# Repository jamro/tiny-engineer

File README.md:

# Tiny Engineer

> Give your AI coding agent a body.

**[Watch the demo](https://youtu.be/RX_QRxdXMjg)** · [Build your own](#build-your-own) · [Community builds](#community-builds) · [How it works](#how-it-works)

A small robot on your desk. It moves, changes its face, and rings a bell as your coding AI agent works.

| Your agent… | The robot… |
| --- | --- |
| Reads files | Looks around |
| Writes code | Types |
| Thinks or waits | Looks up |
| Finishes the task | Rings the bell |

Open source. Print the body, plug the ESP32, servos, OLED, and speaker into the [main control board](docs/hardware/main-control-board.md), flash it, and it joins your Wi-Fi.

**Works with** Claude Code · Cursor · Antigravity — via [`npx -y tiny-engineer setup`](docs/integration.md) — or Codex, Windsurf, and any script that can POST ([integration guide](docs/integration.md) · [HTTP API](docs/api.md)), including speech through [`POST /play`](docs/api.md#post-play).

## Build your own

| | |
| --- | --- |
| **Parts (electronics + 5× SG90 Servos)** | [shopping list](docs/shopping.md): [main control board](docs/hardware/order-main-control-board.md) plus ESP32, servos, OLED, and speaker |
| **Also needed** | 3D printer + filament, or [order prints](docs/3d/order-parts.md); M2 screws; **5 V / ≥2 A** USB supply |
| **Tools** | Plug in the ESP32, servos, OLED, and speaker on the [main control board](docs/hardware/main-control-board.md). Want to add extra modules? [advanced wiring](docs/hardware/wiring.md) |
| **Difficulty** | **Medium** - fair first hardware project for a software engineer, not a one-LED kit. Optional primer: [From Code to Circuits](docs/hardware-for-software-engineers/README.md) |

The default build uses the open-source main control board. Order it from any fab ([how to order](docs/hardware/order-main-control-board.md) · [KiCad](hardware/boards/main-control-board/)). 

If a ~$15–20 assembled board like this would be useful to you, [Vote here 👍 →](https://github.com/jamro/tiny-engineer/discussions/50) → I’m using the interest to decide whether it’s worth developing further.

**Print → Connect → Flash → Assemble** - step-by-step: **[Getting started](docs/getting-started.md)**.

## Community builds

Finished builds, mods, and desk setups live in **[Show and tell](https://github.com/jamro/tiny-engineer/discussions/categories/show-and-tell)** on GitHub Discussions - browse what others made and post photos of yours.

**Built one? [Share in Show and tell →](https://github.com/jamro/tiny-engineer/discussions/categories/show-and-tell)**

## Roadmap

What we are building toward:

- **More agent integrations** - one-command hooks for more IDEs and CLIs
- **Simplified build process** - easier assembly and setup for quicker builds
- **New characters / bodies** - alternate shells and mods
- **Multi-agent desk** - more than one tiny teammate

**[Star Tiny Engineer](https://github.com/jamro/tiny-engineer)** to follow the build.

## How it works

Your agent (or a hook script) sends poses over **Wi‑Fi HTTP** or **USB serial**. The **ESP32-C3** runs the firmware, optional Wi‑Fi/REST, USB CDC control, and drives the servos, face, and speaker.

**Clients**

- **Default** — [`npx -y tiny-engineer`](https://www.npmjs.com/package/tiny-engineer) (`setup` / `hook`) for Cursor, Claude Code, Antigravity (HTTP or `--transport serial`)
- **Advanced** — `POST /anim` ([HTTP API](docs/api.md)) or framed USB serial ([serial.md](docs/serial.md))

Details: [Integrations](docs/integration.md) · [HTTP API](docs/api.md) · [USB serial](docs/serial.md) · [Cursor hooks](docs/hooks.md)

## Documentation

| You want to… | Start here |
| --- | --- |
| Build the robot | [Getting started](docs/getting-started.md) |
| Buy parts | [Shopping list](docs/shopping.md) |
| Flash the board | **[Web flash](https://jamro.github.io/tiny-engineer/flash/)** · [Flash](docs/flash.md) |
| Assemble the prints | [Assembly](docs/3d/assembly.md) |
| Print the parts | [3D models](3d_models/README.md) |
| Hook up an agent | [Integrations](docs/integration.md) |
| Call the HTTP API | [API](docs/api.md) |
| Anything else | [Docs index](docs/README.md) |

Print it, connect it, change the CAD, or hook up another agent. Issues and PRs welcome - especially new integrations. [CONTRIBUTING.md](CONTRIBUTING.md) · [SECURITY.md](SECURITY.md) · [CODE_OF_CONDUCT.md](CODE_OF_CONDUCT.md)

## License

- **Software** (firmware, integrations, scripts, documentation) — [MIT](LICENSE)
- **Hardware designs** (CAD source and printables in [`3d_models/`](3d_models/) and under [`mods/*/3d_models/`](mods/); KiCad PCBs in [`hardware/`](hardware/)) — [CERN-OHL-S-2.0](3d_models/LICENSE)

See [LICENSING.md](LICENSING.md) for scope and effective date. The **Tiny Engineer** name and logo are not licensed - see [TRADEMARK.md](TRADEMARK.md).

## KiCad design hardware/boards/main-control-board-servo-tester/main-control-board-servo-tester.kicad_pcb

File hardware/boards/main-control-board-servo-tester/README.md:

# main-control-board-servo-tester

Plug that seats on one servo column of the main control board. A red LED shows 5 V. A yellow LED shows the signal.

- **Status:** draft
- **KiCad:** 10
- **Interfaces:** J1, 1x03 socket. Pin 1 signal (schematic net `+3.3V`) through R1 470 Ω to yellow D1. Pin 2 `+5V` through R2 1 kΩ to red D2. Pin 3 GND. Both LED cathodes go to GND.
- **Assumptions:** Seat J1 so the silk labels match the main-board column: PWM to PWM, +5V to 5 V, GND to GND. Read those labels on both boards before plugging in. The capacitor beside the servo header blocks the other orientation. Pin 1 on this tester is the signal pin; it meets the PWM pin of the column, not pin 1. Only the Default net class. Power comes from the column under test.
- **Built:** not manufactured
- **Tested:** not tested

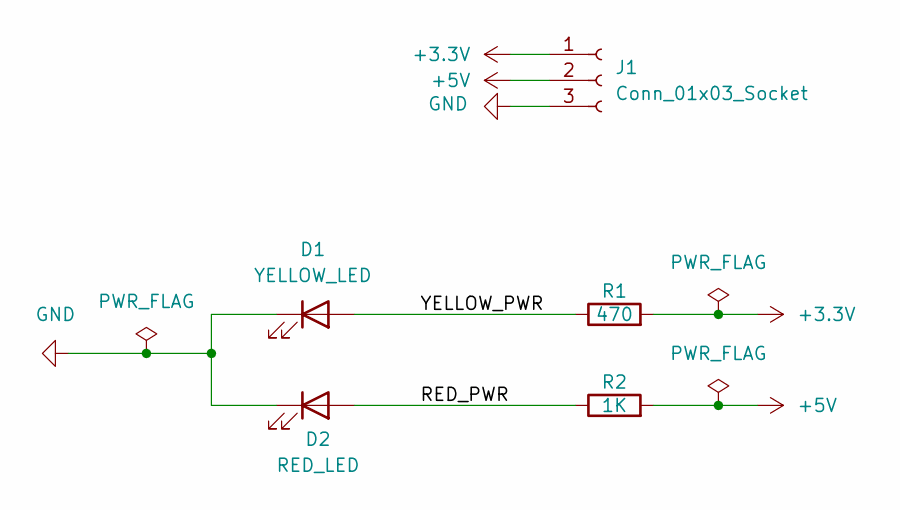
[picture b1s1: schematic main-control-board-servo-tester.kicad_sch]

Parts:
D1: YELLOW_LED; LED_0603_1608Metric; MPN KT-0603Y; LCSC Part # C2287
D2: RED_LED; LED_0603_1608Metric; MPN KT-0603R; LCSC Part # C2286
J1: Conn_01x03_Socket; PinSocket_1x03_P2.54mm_Horizontal; MPN PM254-1-03-W-8.5; LCSC Part # C2897385
R1: 470; R_0603_1608Metric; MPN 0603WAF4700T5E; LCSC Part # C23179
R2: 1K; R_0603_1608Metric; MPN 0603WAF1001T5E; LCSC Part # C21190

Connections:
+3.3V: J1.1, R1.2
+5V: J1.2, R2.2
/RED_PWR: D2.2 (A), R2.1
/YELLOW_PWR: D1.2 (A), R1.1
GND: D1.1 (K), D2.1 (K), J1.3

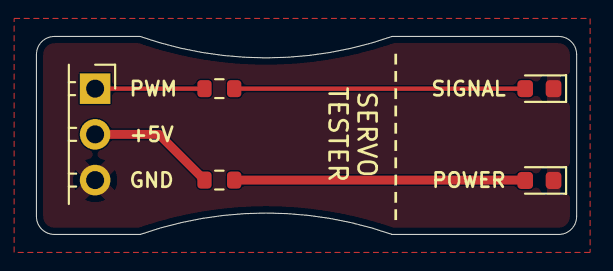
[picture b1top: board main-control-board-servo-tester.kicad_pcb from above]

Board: 2 copper layers, 30.0 x 11.0 mm, 5 parts (0 on the bottom side), 5 nets.

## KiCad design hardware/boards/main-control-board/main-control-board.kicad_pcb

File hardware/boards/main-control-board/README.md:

# main-control-board

This board drives the robot's servos and speaker. Power and USB data come in on a USB-C connector. The Waveshare ESP32-C3-Zero is not soldered down; it plugs into two 9-pin sockets.

- **Status:** tested
- **KiCad:** 10
- **Built:** manufactured and tested
- **Tested:** reference boards ordered and checked; each independent fab run can still differ

## Soldered on the board

The servo driver, the speaker amplifier, and the USB-C connector are parts on this PCB. They replace the plug-in PCA9685 board, the MAX98357A breakout, and the Adafruit 5993 USB-C breakout.

- **PCA9685** drives up to 16 PWM channels. This robot uses five of them for the servos. The I2C address is `0x40`: the address pins and the external-clock pin are tied to ground, so the chip uses its own clock.
- **Servo header** takes five servo plugs. Each plug has ground, 5 V, and a PWM signal.
- **MAX98357A** is the mono class-D amplifier. The speaker connects to a 2-pin header. The speaker's minus terminal is not ground. Connect the speaker only between the two amplifier outputs.
- **USB-C connector** supplies 5 V and the USB data pair. Two 5.1 kΩ resistors on the CC pins mark this board as a USB device. The charger decides how much current is available.
- A **3 A resettable fuse** sits between USB power and the 5 V rail.
- A **TPS259571** eFuse (`U4`) sits between that 5 V rail and servo 5 V. Current limit is set by `R14` (1 kΩ ≈ 2 A). On fault the device auto-retries.
- **OLED header** is for the SSD1306 display. Pin order, from pin 1: 3.3 V, ground, SDA, SCL.
- A second header shares that I2C bus. Its pin order is different: ground, 3.3 V, SDA, SCL.
- A **12-pin extension port** (`J4`) breaks out `SERVO_5V`, two grounds, `+3.3V`, I2S BCLK/LRC, and GPIOs GP6–GP9 / GP20 / GP21.
  - GP8 and GP9 are ESP32-C3 strapping pins. Do not pull them low at reset; GP9 low enters download mode.
  - GP20 and GP21 are the default UART0 RX/TX. Boot log output appears on GP21 at power-up.

A solder jumper next to the amplifier is marked as a 6 dB gain limit.

## What still plugs in

The **Waveshare ESP32-C3-Zero** plugs into two 9-pin sockets, one for each row of pins on the module. This board has no ESP32 chip of its own.

The OLED module plugs into the OLED header.

## Power

USB-C 5 V goes through the fuse onto the `+5V` rail. That rail feeds the ESP32 5 V pin, a 5 V indicator LED, and the eFuse input.

The eFuse output is `SERVO_5V`. That rail feeds the servo plugs (PCA9685 V+), a bulk capacitor, and — through a net tie — the amplifier 5 V net, so the amp supply can still be routed on its own but comes from the protected servo rail, not raw `+5V`.

3.3 V comes from the regulator on the ESP32 module. This board does not have a 3.3 V regulator. 3.3 V feeds the PCA9685 logic supply, the OLED, the I2C pull-ups (4.7 kΩ), the pull-up on the PCA9685 output-enable pin (10 kΩ), and a 3.3 V indicator LED.

Servo 5 V and logic 3.3 V stay separate. They share ground.

Use a **5 V supply of at least 2 A**. Five stalled servos can draw more than a typical USB port provides. Multi-servo stall can also hit the eFuse’s ~2 A limit before the 3 A resettable fuse trips.

## Connections from the ESP32

| Function | ESP32 pin | Goes to |
| --- | --- | --- |
| I2C SDA | GP0 | PCA9685 and OLED |
| I2C SCL | GP1 | PCA9685 and OLED |
| I2S bit clock | GP2 | MAX98357A BCLK |
| I2S word clock | GP3 | MAX98357A LRC |
| I2S data | GP4 | MAX98357A DIN |
| Servo output enable | GP5 | PCA9685 output enable (active low) |
| USB D− | GPIO18 | USB-C |
| USB D+ | GPIO19 | USB-C |

GP5 drives PCA9685 OE (`PCA9685_OE_WIRED` in [`include/pins.h`](../../../include/pins.h)). A 10 kΩ pull-up holds OE high until firmware drives it low after neutral park.

## Board

Two-layer FR4, about 1.6 mm thick.

5 V tracks (`+5V` and `SERVO_5V`) are 1.5 mm wide. 3.3 V tracks are 0.4 mm. The amplifier 5 V net is 0.5 mm. USB data tracks use their own width.

The two ESP32 sockets follow the Waveshare header. Pad 1 is 5 V. Pads count anticlockwise from the module's USB connector. Those numbers are the module's header pads, not the pins of the ESP32-C3 chip.

## Library exceptions

### USB1 3D model (C2765186)

Footprint `USB-C-SMD_TYPE-C-16PIN-2MD-073` loads `USB-C-SMD_TYPE-C-6PIN-2MD-073.{wrl,step}`.

EasyEDA has no separate `…16PIN….wrl` for this LCSC part. Official package `c_para.3DModel` is `USB-C-SMD_TYPE-C-6PIN-2MD-073` (outline3D uuid `4ee8413127e64716b804db03d4b340ae`). Re-import via `import_lcsc.py --lcsc-id C2765186` reproduces the same mapping.

Do not rename or replace the model only to silence filename-mismatch reviews — this is intentional.

Contribution rules: [`docs/pcb.md`](../../../docs/pcb.md).

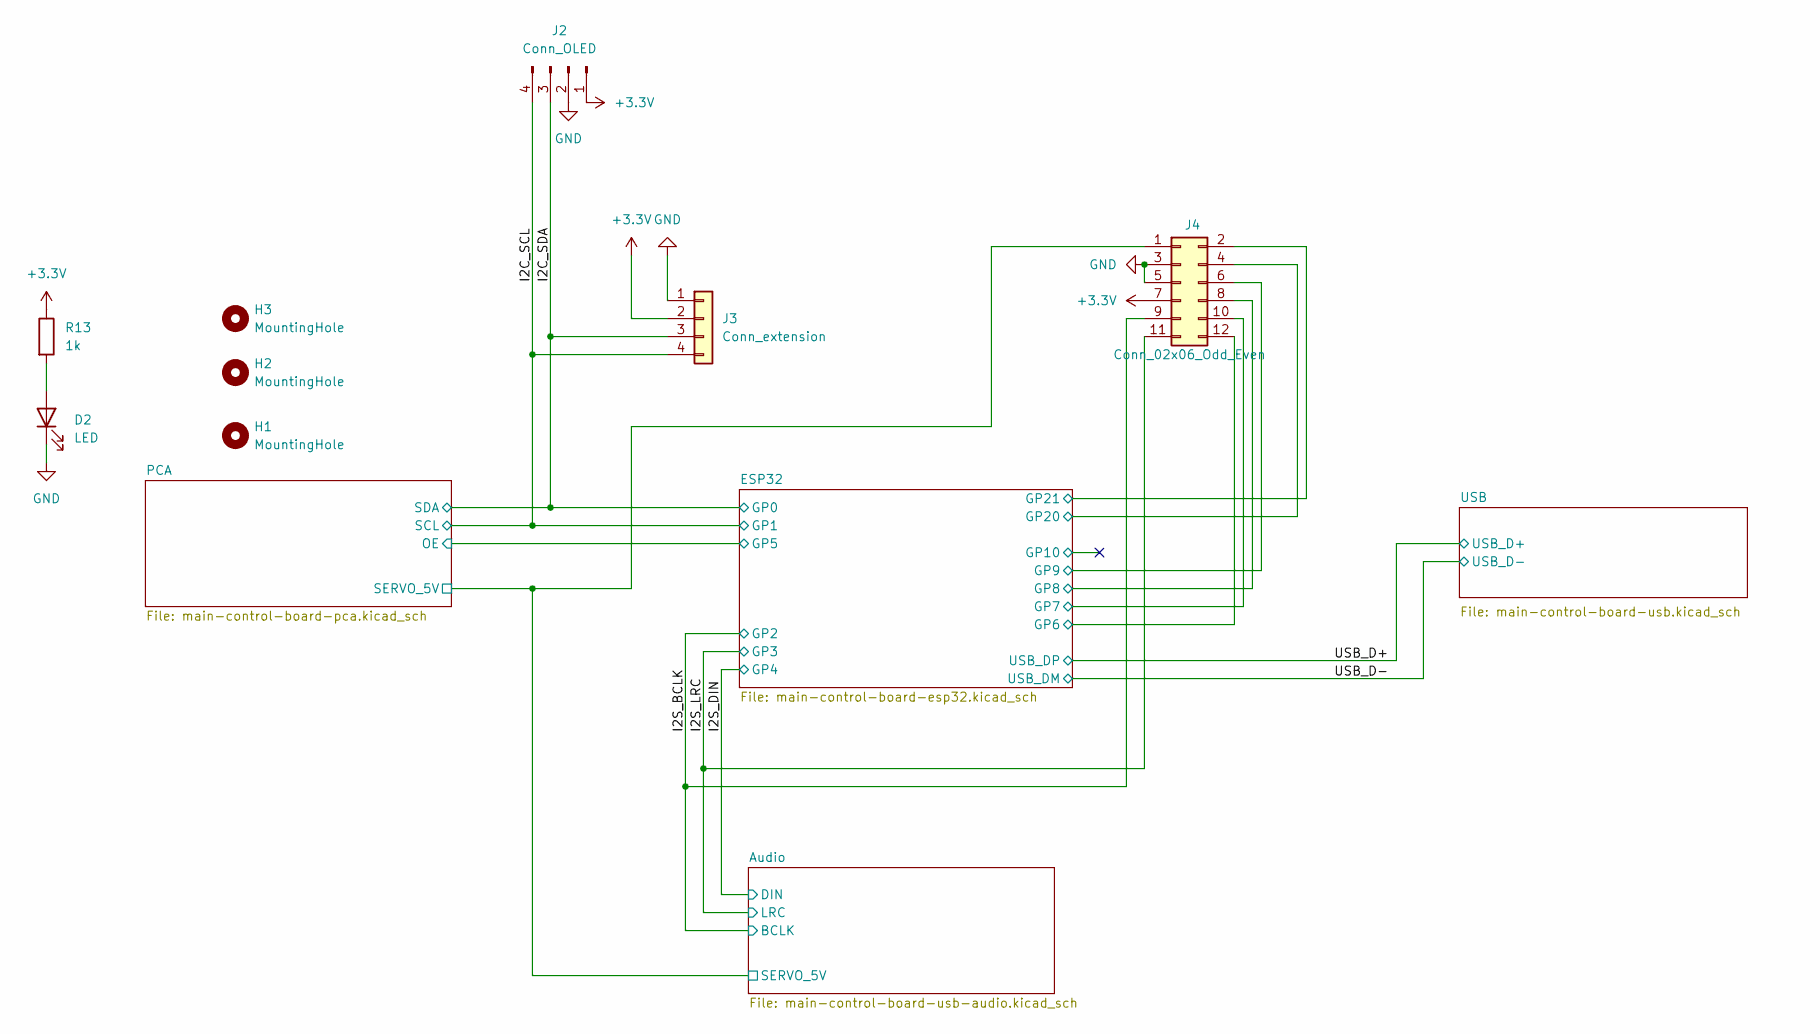
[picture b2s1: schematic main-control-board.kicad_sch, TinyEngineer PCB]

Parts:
D2: LED; LED_0603_1608Metric; MPN KT-0603R; LCSC Part # C2286
H1, H2, H3: MountingHole; MountingHole_2.2mm_M2
J2: Conn_OLED; PinHeader_1x04_P2.54mm_Vertical; MPN PZ254V-11-04P; LCSC Part # C2691448
J3: Conn_extension; JST_SH_SM04B-SRSS-TB_1x04-1MP_P1.00mm_Horizontal; MPN SM04B-SRSS-TB(LF)(SN); LCSC Part # C160404
J4: Conn_02x06_Odd_Even; PinHeader_2x06_P2.54mm_Vertical
R13: 1k; R_0603_1608Metric; MPN 0603WAF1001T5E; LCSC Part # C21190

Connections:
+3.3V: J2.1, J3.2, J4.7, R13.1; also elsewhere on the board
/ESP32/GP6: J4.12; also elsewhere on the board
/ESP32/GP7: J4.10; also elsewhere on the board
/ESP32/GP8: J4.8; also elsewhere on the board
/ESP32/GP9: J4.6; also elsewhere on the board
/ESP32/GP20: J4.4; also elsewhere on the board
/ESP32/GP21: J4.2; also elsewhere on the board
/I2C_SCL: J2.4, J3.4; also elsewhere on the board
/I2C_SDA: J2.3, J3.3; also elsewhere on the board
/I2S_BCLK: J4.9; also elsewhere on the board
/I2S_LRC: J4.11; also elsewhere on the board
/PCA/SERVO_5V: J4.1; also elsewhere on the board
GND: D2.1 (K), J2.2, J3.1, J4.3, J4.5; also elsewhere on the board
unnamed: D2.2 (A), R13.2

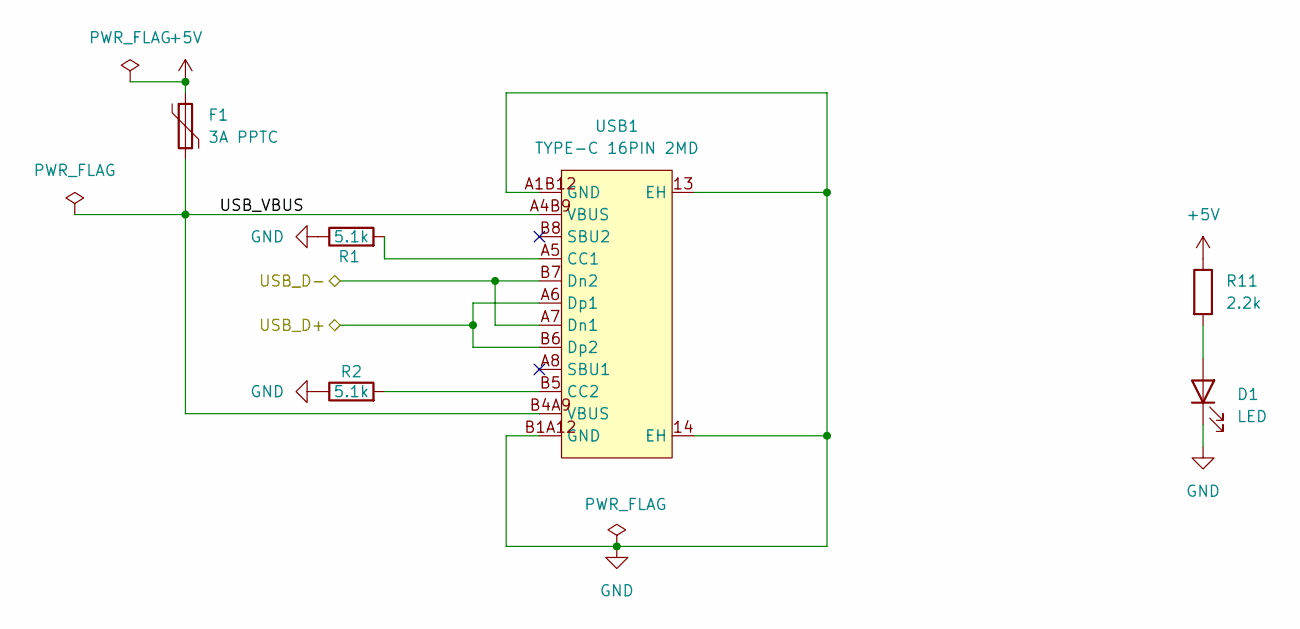
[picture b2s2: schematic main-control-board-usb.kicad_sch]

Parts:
D1: LED; LED_0603_1608Metric; MPN KT-0603R; LCSC Part # C2286
F1: 3A PPTC; Fuse_1812_4532Metric; MPN BSMD1812-300-16V; LCSC Part # C883162
R1, R2: 5.1k; R_0603_1608Metric; MPN 0603WAF5101T5E; LCSC Part # C23186
R11: 2.2k; R_0603_1608Metric; MPN 0603WAF2201T5E; LCSC Part # C4190
USB1: TYPE-C 16PIN 2MD; USB-C-SMD_TYPE-C-16PIN-2MD-073; MPN TYPE-C 16PIN 2MD(073); LCSC Part # C2765186

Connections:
+5V: F1.1, R11.1; also elsewhere on the board
/USB/USB_VBUS: F1.2, USB1.A4B9 (VBUS), USB1.B4A9 (VBUS)
/USB_D+: USB1.A6 (Dp1), USB1.B6 (Dp2); also elsewhere on the board
/USB_D-: USB1.A7 (Dn1), USB1.B7 (Dn2); also elsewhere on the board
GND: D1.1 (K), R1.1, R2.1, USB1.13 (EH), USB1.14 (EH), USB1.A1B12 (GND), USB1.B1A12 (GND); also elsewhere on the board
unnamed: D1.2 (A), R11.2
unnamed: R1.2, USB1.A5 (CC1)
unnamed: R2.2, USB1.B5 (CC2)

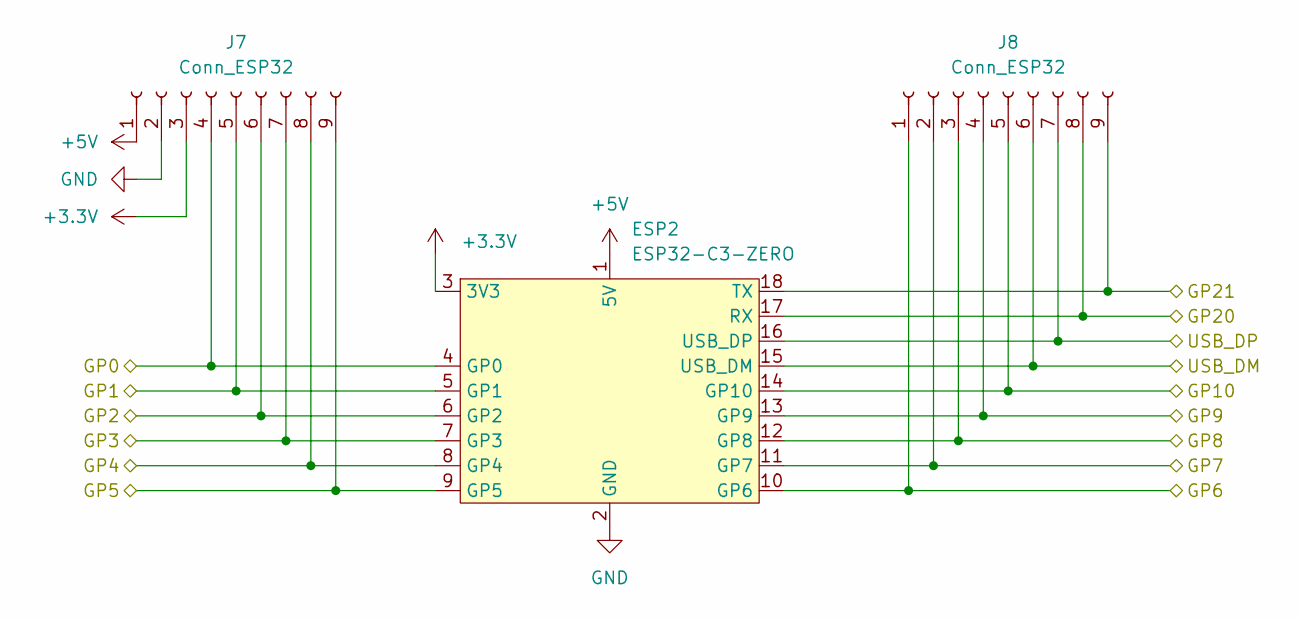
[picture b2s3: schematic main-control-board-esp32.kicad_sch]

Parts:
ESP2: ESP32-C3-ZERO; ESP32_C3_Zero_Dev_Board
J7, J8: Conn_ESP32; PinSocket_1x09_P2.54mm_Vertical; MPN PM254-1-09-Z-8.5; LCSC Part # C2897372

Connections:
+3.3V: ESP2.3 (3V3), J7.3; also elsewhere on the board
+5V: ESP2.1 (5V), J7.1; also elsewhere on the board
/ESP32/GP5: ESP2.9 (GP5), J7.9; also elsewhere on the board
/ESP32/GP6: ESP2.10 (GP6), J8.1; also elsewhere on the board
/ESP32/GP7: ESP2.11 (GP7), J8.2; also elsewhere on the board
/ESP32/GP8: ESP2.12 (GP8), J8.3; also elsewhere on the board
/ESP32/GP9: ESP2.13 (GP9), J8.4; also elsewhere on the board
/ESP32/GP10: ESP2.14 (GP10), J8.5
/ESP32/GP20: ESP2.17 (RX), J8.8; also elsewhere on the board
/ESP32/GP21: ESP2.18 (TX), J8.9; also elsewhere on the board
/I2C_SCL: ESP2.5 (GP1), J7.5; also elsewhere on the board
/I2C_SDA: ESP2.4 (GP0), J7.4; also elsewhere on the board
/I2S_BCLK: ESP2.6 (GP2), J7.6; also elsewhere on the board
/I2S_DIN: ESP2.8 (GP4), J7.8; also elsewhere on the board
/I2S_LRC: ESP2.7 (GP3), J7.7; also elsewhere on the board
/USB_D+: ESP2.16 (USB_DP), J8.7; also elsewhere on the board
/USB_D-: ESP2.15 (USB_DM), J8.6; also elsewhere on the board
GND: ESP2.2 (GND), J7.2; also elsewhere on the board

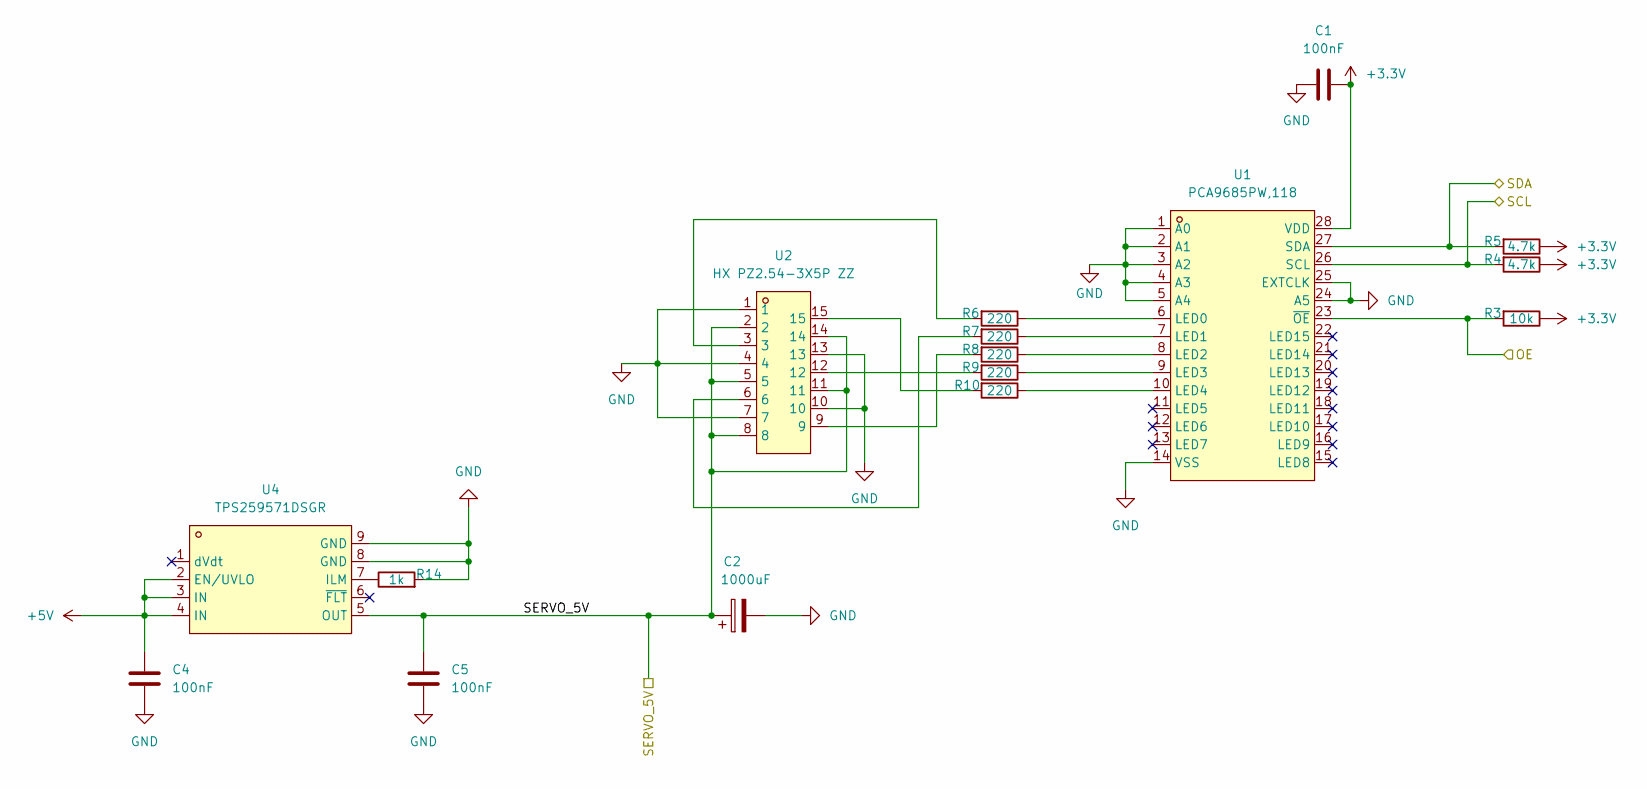
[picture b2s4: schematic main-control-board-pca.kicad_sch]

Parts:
C1, C4, C5: 100nF; C_0603_1608Metric; MPN CC0603KRX7R9BB104; LCSC Part # C14663
C2: 1000uF; CP_Elec_10x10.5; MPN JVJ16V1000M10x10; LCSC Part # C46550395
R3: 10k; R_0603_1608Metric; MPN 0603WAF1002T5E; LCSC Part # C25804
R4, R5: 4.7k; R_0603_1608Metric; MPN 0603WAF4701T5E; LCSC Part # C23162
R6, R7, R8, R9, R10: 220; R_0603_1608Metric; MPN 0603WAF2200T5E; LCSC Part # C22962
R14: 1k; R_0603_1608Metric; MPN 0603WAF1001T5E; LCSC Part # C21190
U1: PCA9685PW,118; TSSOP-28_L9.7-W4.4-P0.65-LS6.4-TL; MPN PCA9685PW,118; LCSC Part # C2678753
U2: HX PZ2.54-3X5P ZZ; HDR-TH_15P-P2.54-V-M-R3-C5-S7.5; MPN HX PZ2.54-3x5P ZZ; LCSC Part # C32713292
U4: TPS259571DSGR; WSON-8_L2.0-W2.0-P0.50-TL-EP; MPN TPS259571DSGR; LCSC Part # C471038

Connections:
+3.3V: C1.2, R3.1, R4.1, R5.1, U1.28 (VDD); also elsewhere on the board
+5V: C4.2, U4.2 (EN/UVLO), U4.3 (IN), U4.4 (IN); also elsewhere on the board
/ESP32/GP5: R3.2, U1.23 (~OE); also elsewhere on the board
/I2C_SCL: R4.2, U1.26 (SCL); also elsewhere on the board
/I2C_SDA: R5.2, U1.27 (SDA); also elsewhere on the board
/PCA/SERVO_5V: C2.1, C5.2, U2.2, U2.5, U2.8, U2.11, U2.14, U4.5 (OUT); also elsewhere on the board
GND: C1.1, C2.2, C4.1, C5.1, R14.2, U1.1 (A0), U1.2 (A1), U1.3 (A2), U1.4 (A3), U1.5 (A4), U1.14 (VSS), U1.24 (A5), U1.25 (EXTCLK), U2.1, U2.4, U2.7, U2.10, U2.13, U4.8 (GND), U4.9 (GND); also elsewhere on the board
unnamed: R6.2, U2.3
unnamed: R7.2, U2.6
unnamed: R8.2, U2.9
unnamed: R9.2, U2.12
unnamed: R10.2, U2.15
unnamed: R6.1, U1.6 (LED0)
unnamed: R7.1, U1.7 (LED1)
unnamed: R8.1, U1.8 (LED2)
unnamed: R9.1, U1.9 (LED3)
unnamed: R10.1, U1.10 (LED4)
unnamed: R14.1, U4.7 (ILM)
unnamed 38: U4.1 (dVdt); also elsewhere on the board

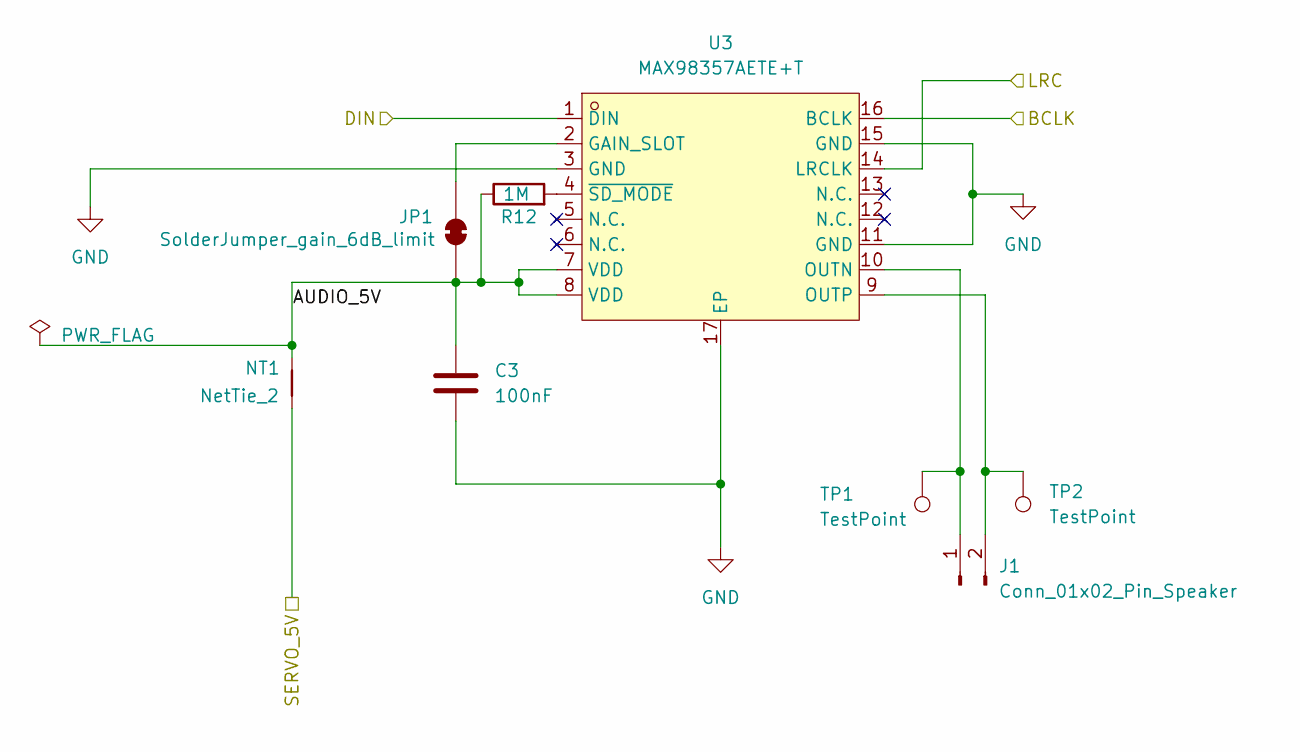
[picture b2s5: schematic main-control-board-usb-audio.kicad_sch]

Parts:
C3: 100nF; C_0603_1608Metric; MPN CC0603KRX7R9BB104; LCSC Part # C14663
J1: Conn_01x02_Pin_Speaker; Molex_PicoBlade_53261-0271_1x02-1MP_P1.25mm_Horizontal; MPN HC-1.25-2PWT; LCSC Part # C2845379
JP1: SolderJumper_gain_6dB_limit; SolderJumper-2_P1.3mm_Bridged_RoundedPad1.0x1.5mm
NT1: NetTie_2; NetTie-2_SMD_Pad2.0mm
R12: 1M; R_0603_1608Metric; MPN 0603WAF1004T5E; LCSC Part # C22935
TP1, TP2: TestPoint; SolderWire-0.25sqmm_1x01_D0.65mm_OD2mm
U3: MAX98357AETE+T; TQFN-16_L3.0-W3.0-P0.50-BL-EP1.5; MPN MAX98357AETE+T; LCSC Part # C910544

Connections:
/Audio/AUDIO_5V: C3.2, JP1.1 (A), NT1.2, R12.1, U3.7 (VDD), U3.8 (VDD)
/I2S_BCLK: U3.16 (BCLK); also elsewhere on the board
/I2S_DIN: U3.1 (DIN); also elsewhere on the board
/I2S_LRC: U3.14 (LRCLK); also elsewhere on the board
/PCA/SERVO_5V: NT1.1; also elsewhere on the board
GND: C3.1, U3.3 (GND), U3.11 (GND), U3.15 (GND), U3.17 (EP); also elsewhere on the board
unnamed: J1.1, TP1.1 (1_1), U3.10 (OUTN)
unnamed: J1.2, TP2.1 (1_1), U3.9 (OUTP)
unnamed: JP1.2 (B), U3.2 (GAIN_SLOT)
unnamed: R12.2, U3.4 (~SD_MODE)

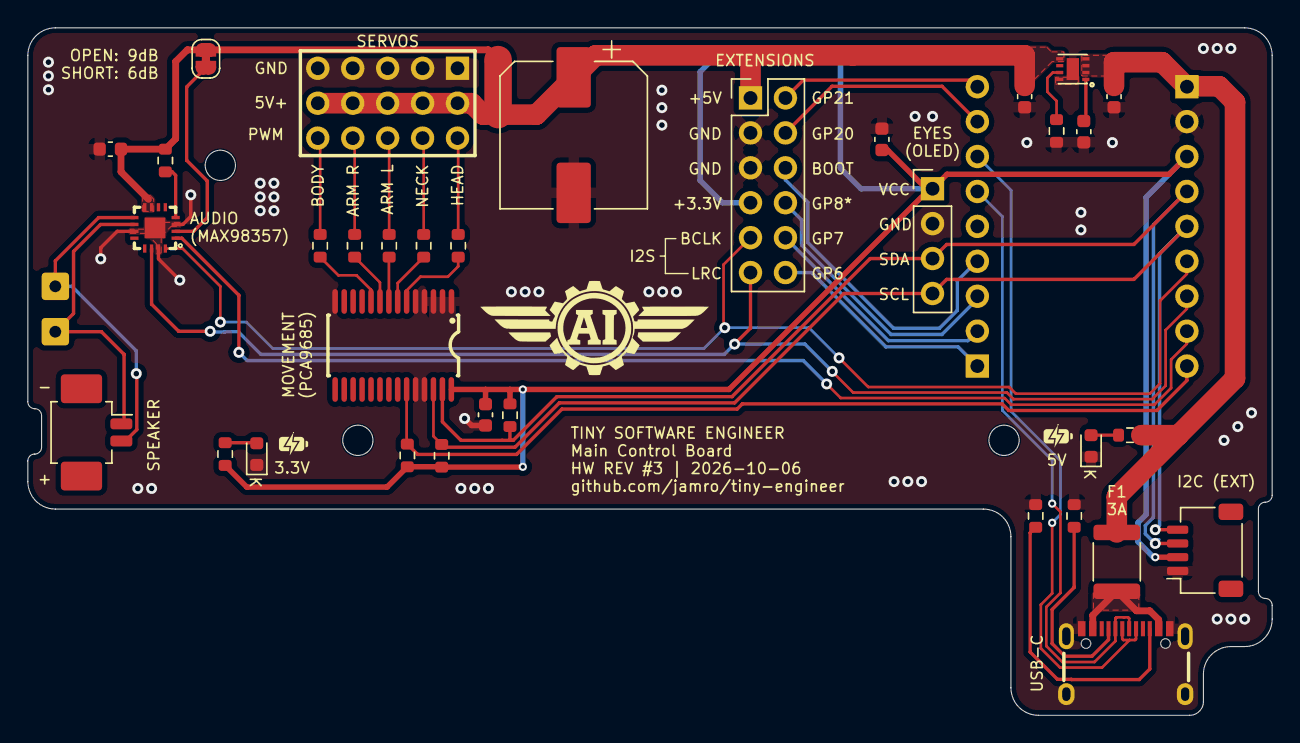
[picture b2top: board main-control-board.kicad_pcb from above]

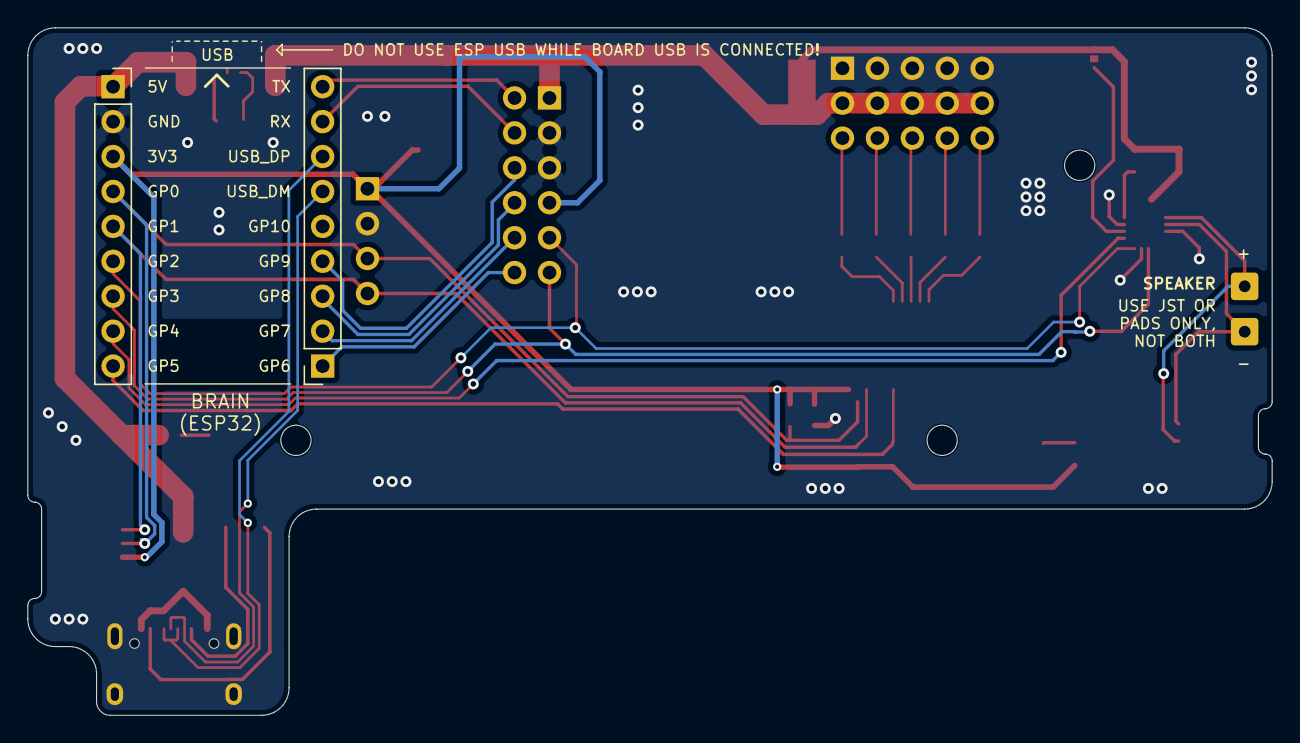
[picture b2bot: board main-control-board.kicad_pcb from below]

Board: 2 copper layers, 90.5 x 50.0 mm, 42 parts (2 on the bottom side), 40 nets.

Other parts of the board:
C6, C7: 100nF; C_0603_1608Metric

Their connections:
+3.3V: C7.1; also elsewhere on the board
GND: C6.2, C7.2; also elsewhere on the board
unnamed 38: C6.1; also elsewhere on the board

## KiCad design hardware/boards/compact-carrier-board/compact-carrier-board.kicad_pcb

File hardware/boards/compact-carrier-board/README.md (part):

# compact-carrier-board

Small distribution PCB that sits under the ESP32-C3-Zero where it mounts through
the desk's ESP slot, fanning its I2C/I2S/power pins out to the PCA9685, OLED,
MAX98357A amp, and servo power — instead of point-to-point wiring.

- **Status:** in review
- **KiCad:** 10
- **Interfaces:** ESP32-C3-Zero 2×9 socket, `J_PWR` (5V/GND + external USB
  D+/D-), `J_SERVO`, `J_I2C_OLED`, `J_I2C_PCA`, `J_I2S`
- **Assumptions:** sized against the desk generated with the **PowerHD
  HD-1370A** servo preset (`servos.json`) — the SG90 and FS0307 presets
  produce different desk dimensions per the parametric design docs, and this
  board's fit has **not** been verified against either of them. Re-check the
  ESP slot dimensions in your own exported desk model before relying on this
  outline if you're on a different preset. See `docs/hardware/interfaces.md`
  for the canonical net map (5V/3.3V domains, GP0-GP4 assignments); this
  board implements that map in copper.
- **Built:** the `carrier-fab-v3-replacement_Y5` upload was produced and
  shipped by JLCPCB (not yet received). That batch carries the **mirrored
  socket map this revision fixes** — see "Mirrored socket map (boards in
  transit)" below for the assembly workaround. Its drilling is fine: the Y5
  drill export is a single 0.9mm tool over all 37 holes and JLC's own CAM
  layer a single aperture, so the 7-undersized-hole defect of the earlier
  `_Y3` upload never reached a physical board.

## Files

- `compact-carrier-board.kicad_pcb` — KiCad 10 board source
- `compact-carrier-board.kicad_pro` — KiCad 10 project file (no `.kicad_sch`
  — this board has no schematic, laid out directly from footprints)
- `carrier-board-render.png` — 3D top render, regenerated with
  `kicad-cli pcb render --side top` after the row swap and silk additions

Gerbers, drill, BOM, and CPL are generated outputs, not source — regenerate
them from `compact-carrier-board.kicad_pcb` when ordering rather than
relying on a committed copy. `J_ESP1`/`J_ESP2` carry real `Value`/`LCSC`
fields and each footprint has a real origin at its own center, so
`kicad-cli pcb export pos` produces correct positions directly (verified:
`(13.00, -16.89)` / `(13.00, -1.65)`) — no manual patching. `J_PWR`,
`J_SERVO`, `J_I2C_OLED`, `J_I2C_PCA`, and `J_I2S` are flagged
`exclude_from_bom`/`exclude_from_pos_files` so they never appear in either
export. There's no `.kicad_sch`, so `kicad-cli` has no BOM-export
subcommand for this board (that's a schematic-only feature) — a BOM script
or fab-tool plugin reading the `.kicad_pcb`'s footprint properties directly
now gets correct `Value`/`LCSC` without hand-derivation.

## Assembly: only the ESP header strips are populated parts

`J_PWR`, `J_SERVO`, `J_I2C_OLED`, `J_I2C_PCA`, and `J_I2S` are bare
through-holes for direct wire connections, not connector footprints to
populate — excluded from BOM/CPL at the footprint level (see above).

`J_ESP1`/`J_ESP2` are the one real part: **Kinghelm KH-2.54FH-1X9P-H3.5**
(LCSC/JLCPCB `C55778388`), a 2.54mm 1×9 THT female header. There's no 2×9 part
— the
ESP32-C3-Zero's socket needs **two** of these strips, one per row. The board
models this as two separate footprint objects, **`J_ESP1`** (the inner row,
nearer the wire end: 5V/GND/3V3/GPIO0-5) and **`J_ESP2`** (the outer row,
nearest the slot edge: GPIO21-GPIO6), each a real
9-pad object with its own designator — not one 2×9 footprint with a
quantity hint in prose. JLCPCB's assembly tooling (and most BOM tooling)
determines quantity by counting designators, not by parsing Comment text, so
a generated BOM lists both on one row as `"J_ESP1,J_ESP2"` (identical part,
JLC's own convention for grouping identical components) — that reads as qty
2 unambiguously.

A generated CPL has one row per designator, `J_ESP1` and `J_ESP2`, each at
its own row's real center — (13.00, 16.89) and (13.00, 1.65) in the board's
own coordinates — read directly by `kicad-cli pcb export pos` from each
footprint's own origin, no hand-derivation needed.

## Why this shape

Measured directly from an exported desk part (not estimated): the ESP mounting
slot is 25.0 × 18.5mm, and three of its four sides sit only 3.0–3.6mm from
full-height enclosure walls — too tight for any connector housing. Only the
front is open. That forced the layout:

- **26 × 44mm**, 2-layer.
- Back 18.5mm: 2×9 female socket for the ESP32-C3-Zero (2.54mm pitch,
  15.24mm row spacing — Waveshare's documented spec for the Zero board family,
  confirmed within 0.04mm of a direct caliper measurement).
- Front zone: `J_PWR` (now 4-pin — 5V/GND plus the external USB D+/D-, see
  below), `J_SERVO` (5V direct to PCA9685 V+, bypassing the ESP's own 3.3V
  regulator), `J_I2C_OLED`, `J_I2C_PCA` (separate connectors, bus shared via
  on-board copper — no external splitter cable), `J_I2S` (own on-board 5V
  feed for the amp).
- Everything routes fully on-board; nothing needs an off-board jumper.

## Pinout (rows stated in the frame that decides them)

Row placement is the part that is easy to get backwards, so name the rule:
**the pad map, seen from the face the module plugs into, has to be the
module's component-side view.** A pin-side view is the correct drawing only
for a socket on the *opposite* face — that inversion is exactly what went
wrong in the shipped batch (below).

Hold the C3-Zero component side up with its USB-C over this board's 5V-bus
edge (the long edge the 5V trace hugs). Then:

- **Outer row** — `J_ESP2`, nearest the slot edge (y=14.15):
  `GPIO21, GPIO20, GPIO19, GPIO18, GPIO10, GPIO9, GPIO8, GPIO7, GPIO6`.
  Mechanical/no-net support **except GP19 and GP18**, the native USB pair —
  see USB below.
- **Inner row** — `J_ESP1`, nearer the wire end (y=29.39):
  `5V, GND, 3V3, GPIO0(SDA), GPIO1(SCL), GPIO2(BCLK), GPIO3(LRCLK), GPIO4(DIN), GPIO5`

Pins 1 and 18 land at the 5V-bus edge in both rows, and that is what fixes
the module's USB-C to that edge. Traversing 1 to 18 reads counter-clockwise
from above, matching Waveshare's own pinout art (1-9 down the left column,
10-18 up the right, USB-C at the top).

## USB pass-through (external jack, not the C3-Zero's own USB-C)

Per `docs/hardware/interfaces.md`: the robot's single external USB-C (Adafruit
5993) carries both power and the ESP32's native USB D+/D- lines, so flashing
and serial CDC work through the panel-mount jack once the desk is sealed —
the C3-Zero's own onboard USB-C is left unused. No ESD or series-resistor
circuitry is specified for this link; it's a direct connection.

| `J_PWR` pin | Net | Goes to |
| --- | --- | --- |
| 1 | GND | common ground |
| 2 | D+ | ESP32 **GPIO19** (outer-row pad, native USB DP) |
| 3 | D− | ESP32 **GPIO18** (outer-row pad, native USB DM) |
| 4 | 5V | ESP32 5V rail, PCA9685 V+ (via `J_SERVO`), MAX98357A |

D+/D- run down the same 2.54mm grid columns as their own pads (x=20.42 and
22.96), which sits half a pitch off `J_I2C_OLED`/`J_I2C_PCA`'s grid, so they
never cross those connectors' pads on the way past. Since the row swap they
also pass the inner row, where the 3V3 and SDA holes occupy those two
columns, so each line takes one short lateral jog into the adjacent lane
(1.27mm off-axis, 0.42mm to the nearest pad edge) and returns — still F.Cu,
no vias. Each line measures 36.088mm and the two are exactly length-matched;
that is 16mm longer than before the swap, which is electrically unremarkable
at full-speed 12 Mbps.

## Mirrored socket map (boards in transit)

**The shipped boards (`carrier-fab-v3-replacement_Y5`) have the two socket
rows the wrong way round.** Their pad map is the C3-Zero seen from its *pin
side*, which is the correct drawing only for a socket on the opposite face;
as fabricated, a component-side-up module does not mate.

Caught by handedness, which no rotation can change: on the module
(component side, USB-C up) pins 1-9 run DOWN the left column and 10-18 UP
the right, so 1 to 18 is counter-clockwise; on those boards `J_ESP1` 1 to 9
runs left-to-right along the outer row and `J_ESP2` 10 to 18 right-to-left
along the inner row, i.e. clockwise.

**This revision fixes the source** — rows swapped in copper, nothing moved
mechanically. **For the boards in transit, fix it at assembly:** solder both
female strips to the **pour face** (B.Cu) and run that face up. From the
pour face you see the mirror of the F.Cu artwork, which is the
component-side map, so the module mates. What that build costs: the module's
own USB-C ends up over the long edge facing the opposite wall from this
revision's intent (unused either way — the Adafruit 5993 jack carries power
and CDC), the silkscreen ends up underneath so mark pin 1 before assembly,
and the wire-end connector positions mirror left-right, so the runs to the
PCA9685 / OLED / amp swap sides.

## Fab notes

- `kicad-cli pcb drc --severity-all` (KiCad 10.0.6, run *without*
  `--refill-zones` so it judges the on-disk fill) reports **0 violations and
  0 unconnected items** — and that statement now means something. The
  project's DRC floors used to be `min_clearance` 0.0, `min_silk_clearance`
  0.0, `min_text_height` 0.8 and `min_text_thickness` 0.08, so DRC could not
  have failed on clearance, silk overlap or undersized text however bad they
  got. They are now 0.2 / 0.15 / 1.0 / 0.15, matching JLCPCB's floors and
  its standard-font minimum. Schematic parity is not checked and cannot be —
  there is no `.kicad_sch` for this board, and `--schematic-parity` answers
  "Schematic parity tests require a fully annotated schematic".
- **Every pad on the board is named on silk.** The socket rows carry
  `GP21`-`GP6` (outer) and `5V, GND, 3V3, GP0`-`GP5` (inner) with a `USB`
  arrow pointing at the 5V-bus edge; each wire-end connector carries its own
  pin names (`3V3/SDA/SCL/GND` on both I2C headers, `5V/BCLK/LRC/DIN/GND` on
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
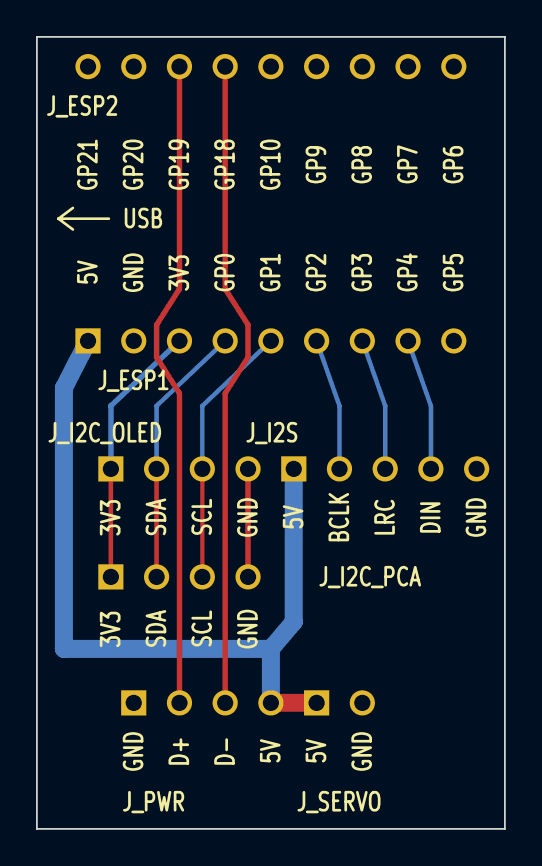
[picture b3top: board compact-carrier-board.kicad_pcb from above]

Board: 2 copper layers, 26.0 x 44.0 mm, 7 parts (0 on the bottom side), 10 nets.

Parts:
J_ESP1: Kinghelm KH-2.54FH-1X9P-H3.5; J_ESP1
J_ESP2: Kinghelm KH-2.54FH-1X9P-H3.5; J_ESP2
J_I2C_OLED: J_I2C_OLED
J_I2C_PCA: J_I2C_PCA
J_I2S: J_I2S
J_PWR: J_PWR
J_SERVO: J_SERVO

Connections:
3V3: J_ESP1.3, J_I2C_OLED.1, J_I2C_PCA.1
5V: J_ESP1.1, J_I2S.1, J_PWR.4, J_SERVO.1
BCLK: J_ESP1.6, J_I2S.2
DIN: J_ESP1.8, J_I2S.4
GND: J_ESP1.2, J_I2C_OLED.4, J_I2C_PCA.4, J_I2S.5, J_PWR.1, J_SERVO.2
LRCLK: J_ESP1.7, J_I2S.3
SCL: J_ESP1.5, J_I2C_OLED.3, J_I2C_PCA.3
SDA: J_ESP1.4, J_I2C_OLED.2, J_I2C_PCA.2
USB_DM: J_ESP2.15, J_PWR.3
USB_DP: J_ESP2.16, J_PWR.2

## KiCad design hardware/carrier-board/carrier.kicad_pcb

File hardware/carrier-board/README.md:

# ESP32 carrier board (desk-mounted build)

A small distribution PCB that sits under the ESP32-C3-Zero where it mounts through
the desk's ESP slot, fanning its I2C/I2S/power pins out to the PCA9685, OLED,
MAX98357A amp, and servo power — instead of point-to-point wiring.

Sized against the desk generated with the **PowerHD HD-1370A** servo preset
(`servos.json`) — the SG90 and FS0307 presets produce different desk
dimensions per the parametric design docs, and this board's fit has **not**
been verified against either of them. Re-check the ESP slot dimensions in
your own exported desk model before relying on this outline if you're on a
different preset. See `docs/hardware/README.md` for the canonical net map
(5V/3.3V domains, GP0-GP4 assignments); this board
implements that map in copper.

## Files

- `carrier-fab-v3.zip` — Gerbers + Excellon drill, upload directly to a fab
  (JLCPCB, PCBWay, OSHPark, PCBWave, etc.)
- `carrier.kicad_pcb` — KiCad 10 board source
- `carrier-board-render.png` — top-copper preview
- `BOM.csv` / `CPL.csv` — assembly files, **J_ESP only** (see below)

## Assembly: only J_ESP is a populated part

`J_PWR`, `J_SERVO`, `J_I2C_OLED`, `J_I2C_PCA`, and `J_I2S` are bare
through-holes for direct wire connections, not connector footprints to
populate — `BOM.csv`/`CPL.csv` deliberately list nothing for them.

`J_ESP` is the one real part: **Kinghelm KH-2.54FH-1X9P-H3.5** (LCSC/JLCPCB
`C55778388`), a 2.54mm 1×9 THT female header. The board's `J_ESP` footprint
is a single 2×9 pad group, but physically needs **two** of these strips (one
per row) — there's no 2×9 part. `BOM.csv` notes the ×2 quantity against the
one `J_ESP` designator rather than implying a single 2×9 unit exists.

`CPL.csv`'s one `J_ESP` row is the combined 2×9 footprint's bounding-box
center (13.00, 9.27mm in the board's own coordinates), extracted directly
from `carrier.kicad_pcb`'s pad positions — `kicad-cli pcb export pos` reports
(0,0) for every footprint here (this board has no `.kicad_sch`, and every
footprint was written with its own placement at `(at 0 0)` with pads given
in absolute coordinates instead), so positions were pulled straight from the
pad data and Y was negated to match kicad-cli's own X/Y sign convention
(confirmed empirically: patched a known coordinate into a scratch copy and
diffed kicad-cli's export against it, rather than assuming the sign). For
hand-placing the two physical strips: row A centers at (13.00, 1.65), row B
at (13.00, 16.89) — both real values (`row_y_a`/`row_y_b` in the generator),
not estimates; the single CPL row just can't split into two without
inventing a second designator that doesn't exist in the board file.

## Why this shape

Measured directly from an exported desk part (not estimated): the ESP mounting
slot is 25.0 × 18.5mm, and three of its four sides sit only 3.0–3.6mm from
full-height enclosure walls — too tight for any connector housing. Only the
front is open. That forced the layout:

- **26 × 44mm**, 2-layer.
- Back 18.5mm: 2×9 female socket for the ESP32-C3-Zero (2.54mm pitch,
  15.24mm row spacing — Waveshare's documented spec for the Zero board family,
  confirmed within 0.04mm of a direct caliper measurement).
- Front zone: `J_PWR` (now 4-pin — 5V/GND plus the external USB D+/D-, see
  below), `J_SERVO` (5V direct to PCA9685 V+, bypassing the ESP's own 3.3V
  regulator), `J_I2C_OLED`, `J_I2C_PCA` (separate connectors, bus shared via
  on-board copper — no external splitter cable), `J_I2S` (own on-board 5V
  feed for the amp).
- Everything routes fully on-board; nothing needs an off-board jumper.

## Pinout (verified against physical board silkscreen)

ESP32-C3-Zero, row nearest USB-C, top-to-bottom:
`5V, GND, 3V3, GPIO0(SDA), GPIO1(SCL), GPIO2(BCLK), GPIO3(LRCLK), GPIO4(DIN), GPIO5`

The other row (`GPIO21,20,19,18,10,9,8,7,6`) is mechanical/GND support only
**except GP19 and GP18**, which are real signal pads — see USB below.

## USB pass-through (external jack, not the C3-Zero's own USB-C)

Per `docs/hardware/interfaces.md`: the robot's single external USB-C (Adafruit
5993) carries both power and the ESP32's native USB D+/D- lines, so flashing
and serial CDC work through the panel-mount jack once the desk is sealed —
the C3-Zero's own onboard USB-C is left unused. No ESD or series-resistor
circuitry is specified for this link; it's a direct connection.

| `J_PWR` pin | Net | Goes to |
| --- | --- | --- |
| 1 | GND | common ground |
| 2 | D+ | ESP32 **GPIO19** (row B pad, native USB DP) |
| 3 | D− | ESP32 **GPIO18** (row B pad, native USB DM) |
| 4 | 5V | ESP32 5V rail, PCA9685 V+ (via `J_SERVO`), MAX98357A |

D+/D- route dead straight from their row-B pads down to `J_PWR` — no jogging,
since `J_PWR`'s pin spacing was deliberately placed on the same 2.54mm grid
as the ESP footprint itself (offset from `J_I2C_OLED`/`J_I2C_PCA`'s grid by
half a pitch), so the two lines never cross OLED/PCA's pads on the way past.

## Fab notes

- 0 DRC errors, 0 unconnected nets (KiCad 10).
- Tightest feature: 0.15mm copper (GND pour minimum thickness). Comfortably
  inside JLCPCB's 0.127mm floor; sits exactly at PCBWave's 0.15mm floor (their
  recommended safe minimum is 0.20mm) — check their DFM report before ordering
  if using PCBWave.
- Connectors are plain 2.54mm through-hole pads (pin headers + jumpers), not
  JST — real JST-PH footprint dimensions weren't verified at design time.
- 5V trace sized per IPC-2221 (2A, 1oz copper, 10°C rise → ≈0.78mm minimum;
  routed at 1.0mm, 0.6mm only through one short pinch point).

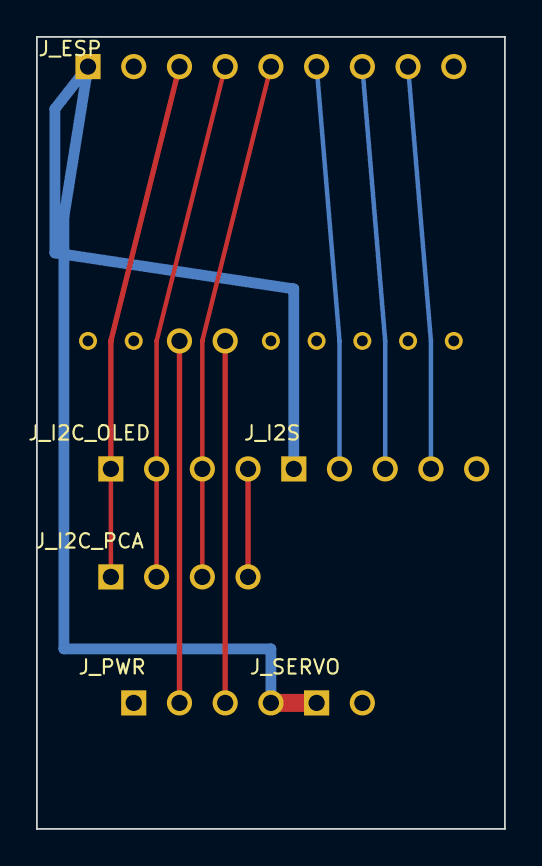
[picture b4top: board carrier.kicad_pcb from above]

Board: 2 copper layers, 26.0 x 44.0 mm, 6 parts (0 on the bottom side), 10 nets.

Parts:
J_ESP: J_ESP
J_I2C_OLED: J_I2C_OLED
J_I2C_PCA: J_I2C_PCA
J_I2S: J_I2S
J_PWR: J_PWR
J_SERVO: J_SERVO

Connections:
3V3: J_ESP.3, J_I2C_OLED.1, J_I2C_PCA.1
5V: J_ESP.1, J_I2S.1, J_PWR.4, J_SERVO.1
BCLK: J_ESP.6, J_I2S.2
DIN: J_ESP.8, J_I2S.4
GND: J_ESP.2, J_I2C_OLED.4, J_I2C_PCA.4, J_I2S.5, J_PWR.1, J_SERVO.2
LRCLK: J_ESP.7, J_I2S.3
SCL: J_ESP.5, J_I2C_OLED.3, J_I2C_PCA.3
SDA: J_ESP.4, J_I2C_OLED.2, J_I2C_PCA.2
USB_DM: J_ESP.15, J_PWR.3
USB_DP: J_ESP.16, J_PWR.2

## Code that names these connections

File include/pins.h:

#pragma once

#include <cstdint>

// =====================================================
// PINOUT
// =====================================================

// I2C -> PCA9685 + OLED
constexpr int I2C_SDA = 0;   // GP0
constexpr int I2C_SCL = 1;   // GP1

// I2S -> MAX98357A
constexpr int I2S_BCLK = 2;  // GP2
constexpr int I2S_LRC  = 3;  // GP3
constexpr int I2S_DIN  = 4;  // GP4

// Extension push-button (J4 pin 4), active-low with internal pull-up when enabled.
constexpr int PUSH_BUTTON_PIN = 20;  // GP20

// Built-in WS2812 RGB
constexpr int RGB_LED_PIN = 10;

// PCA9685 output enable (active LOW). GP5 → OE; default on.
// Set PCA9685_OE_WIRED false only if OE is hard-tied off-chip (e.g. to GND).
constexpr bool PCA9685_OE_WIRED = true;
constexpr int PCA9685_OE_PIN = 5;

// =====================================================
// AUDIO
// =====================================================

// assets/ ships 44100 Hz WAVs; scripts/audio_pack.py halves them while packing LittleFS.
constexpr int SAMPLE_RATE = 22050;

// =====================================================
// PCA9685 / SERVOS
// =====================================================

constexpr uint8_t PCA9685_ADDRESS = 0x40;

constexpr int SERVO_STEP_MS = 10;

// Boot centering / sleep-pose rate (deg/s)
constexpr float SERVO_BOOT_SPEED_DEG_S = 35.0f;

// Servo pulse range
constexpr int SERVO_MIN_US = 800;
constexpr int SERVO_MAX_US = 2200;

// =====================================================
// OLED
// =====================================================

constexpr int OLED_WIDTH  = 128;
constexpr int OLED_HEIGHT = 32;
constexpr uint8_t OLED_ADDRESS = 0x3C;
